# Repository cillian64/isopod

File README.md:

# ISOPOD

ISOPOD is a mobile interactive LED sculpture based on a 2.1m geodesic
isocahedron.  It was displayed at [EMF 2022](https://www.emfcamp.org/).

The outer shell is a 2V geodesic isocahedron made from custom-designed 3d
printed hubs and plastic water pipe.  The core is a regular icosahedron.  12
LED tubes connect to the core's vertices, each made from frosted acrylic tube
and containing a WS2812b addressable LED strip.

The core contains a battery, control electronics, and DC-DC converters.  ISOPOD
is controlled by a Raspberry Pi running software written in Rust.  A custom PCB
mounted on the Pi connects to the battery, DC-DC converters, and LED strips and
adds a battery fuel gauge, GPS module, and 9-axis IMU (accelerometer,
gyroscope, and magnetometer).

ISOPOD was displayed at EMF 2022 with a tether cable (to extend battery life
and avoid it rolling downhill into the lake) but is designed to be totally
wireless, reporting its position and status over Wi-Fi to a backend server.

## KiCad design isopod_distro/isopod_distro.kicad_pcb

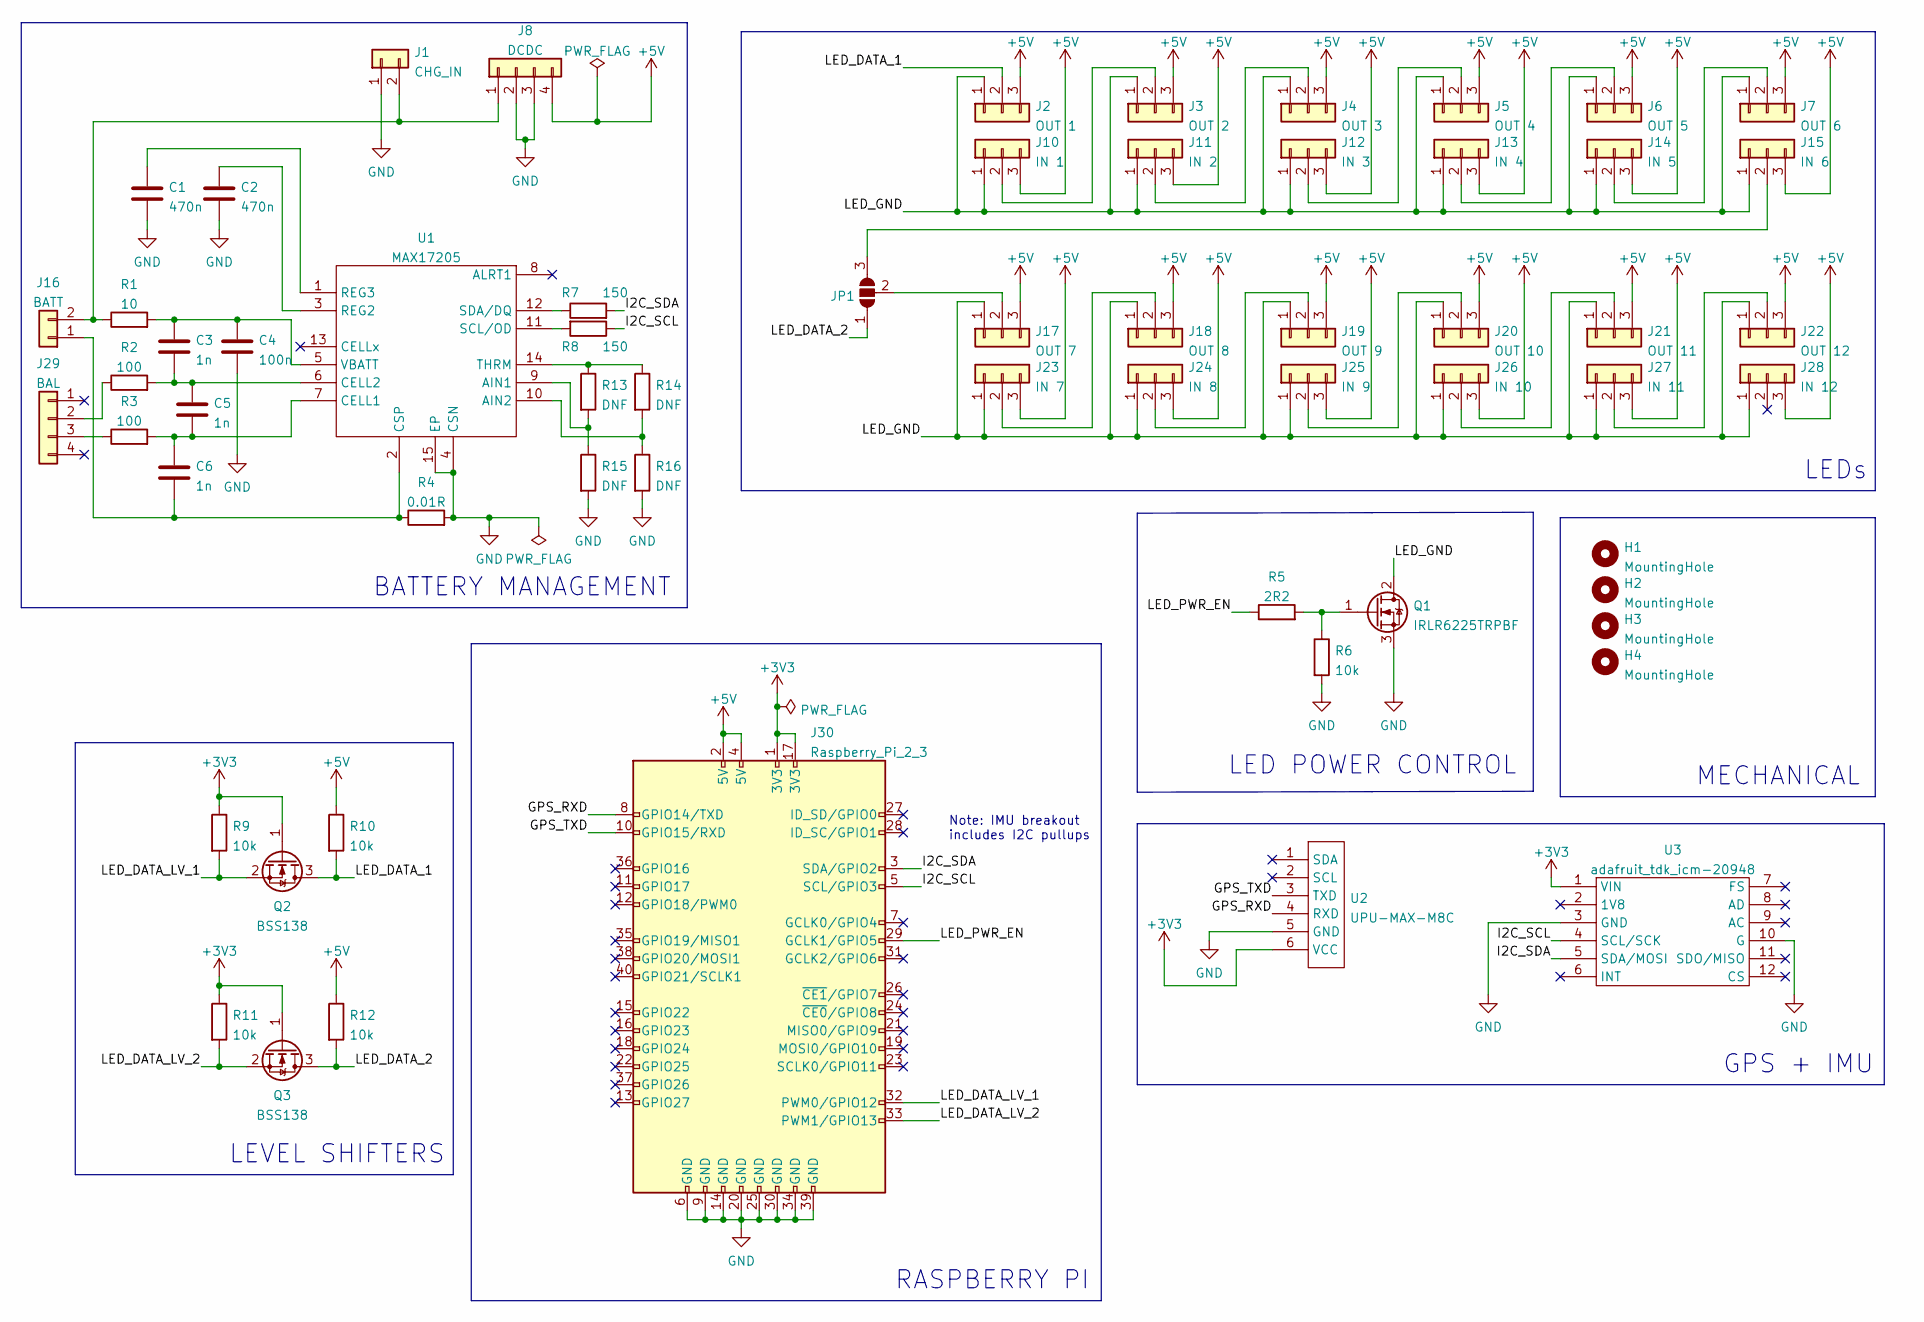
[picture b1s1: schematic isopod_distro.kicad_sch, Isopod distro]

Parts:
C1, C2: 470n; C_0603_1608Metric_Pad1.08x0.95mm_HandSolder
C3, C5, C6: 1n; C_0603_1608Metric_Pad1.08x0.95mm_HandSolder
C4: 100n; C_0603_1608Metric_Pad1.08x0.95mm_HandSolder
H1, H2, H3, H4: MountingHole; MountingHole_2.7mm
J1: CHG_IN; AMASS_XT30U-M_1x02_P5.0mm_Vertical
J2: OUT 1; Molex_KK-254_AE-6410-03A_1x03_P2.54mm_Vertical
J3: OUT 2; Molex_KK-254_AE-6410-03A_1x03_P2.54mm_Vertical
J4: OUT 3; Molex_KK-254_AE-6410-03A_1x03_P2.54mm_Vertical
J5: OUT 4; Molex_KK-254_AE-6410-03A_1x03_P2.54mm_Vertical
J6: OUT 5; Molex_KK-254_AE-6410-03A_1x03_P2.54mm_Vertical
J7: OUT 6; Molex_KK-254_AE-6410-03A_1x03_P2.54mm_Vertical
J8: DCDC; Molex_Mini-Fit_Jr_5566-04A_2x02_P4.20mm_Vertical
J10: IN 1; Molex_KK-254_AE-6410-03A_1x03_P2.54mm_Vertical
J11: IN 2; Molex_KK-254_AE-6410-03A_1x03_P2.54mm_Vertical
J12: IN 3; Molex_KK-254_AE-6410-03A_1x03_P2.54mm_Vertical
J13: IN 4; Molex_KK-254_AE-6410-03A_1x03_P2.54mm_Vertical
J14: IN 5; Molex_KK-254_AE-6410-03A_1x03_P2.54mm_Vertical
J15: IN 6; Molex_KK-254_AE-6410-03A_1x03_P2.54mm_Vertical
J16: BATT; AMASS_XT30U-M_1x02_P5.0mm_Vertical
J17: OUT 7; Molex_KK-254_AE-6410-03A_1x03_P2.54mm_Vertical
J18: OUT 8; Molex_KK-254_AE-6410-03A_1x03_P2.54mm_Vertical
J19: OUT 9; Molex_KK-254_AE-6410-03A_1x03_P2.54mm_Vertical
J20: OUT 10; Molex_KK-254_AE-6410-03A_1x03_P2.54mm_Vertical
J21: OUT 11; Molex_KK-254_AE-6410-03A_1x03_P2.54mm_Vertical
J22: OUT 12; Molex_KK-254_AE-6410-03A_1x03_P2.54mm_Vertical
J23: IN 7; Molex_KK-254_AE-6410-03A_1x03_P2.54mm_Vertical
J24: IN 8; Molex_KK-254_AE-6410-03A_1x03_P2.54mm_Vertical
J25: IN 9; Molex_KK-254_AE-6410-03A_1x03_P2.54mm_Vertical
J26: IN 10; Molex_KK-254_AE-6410-03A_1x03_P2.54mm_Vertical
J27: IN 11; Molex_KK-254_AE-6410-03A_1x03_P2.54mm_Vertical
J28: IN 12; Molex_KK-254_AE-6410-03A_1x03_P2.54mm_Vertical
J29: BAL; JST_XH_B4B-XH-AM_1x04_P2.50mm_Vertical
J30: Raspberry_Pi_2_3; PinHeader_2x20_P2.54mm_Vertical
JP1: SolderJumper_3_Open; SolderJumper-3_P1.3mm_Bridged12_RoundedPad1.0x1.5mm
Q1: IRLR6225TRPBF; TO-252-2; Farnell 2726021
Q2, Q3: BSS138; SOT-23
R1: 10; R_0805_2012Metric_Pad1.20x1.40mm_HandSolder
R2, R3: 100; R_0805_2012Metric_Pad1.20x1.40mm_HandSolder
R4: 0.01R; R_1206_3216Metric_Pad1.30x1.75mm_HandSolder
R5: 2R2; R_0603_1608Metric_Pad0.98x0.95mm_HandSolder
R6, R9, R10, R11, R12: 10k; R_0603_1608Metric_Pad0.98x0.95mm_HandSolder
R7, R8: 150; R_0603_1608Metric_Pad0.98x0.95mm_HandSolder
R13, R14, R15, R16: DNF; R_0603_1608Metric_Pad0.98x0.95mm_HandSolder
U1: MAX17205; TDFN-14-1EP_3x3mm_P0.4mm_EP1.78x2.35mm; Farnell 3404585
U2: UPU-MAX-M8C; upu-max-m8c
U3: adafruit_tdk_icm-20948; adafruit-tdk-icm-20948

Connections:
+3V3: J30.1 (3V3), J30.17 (3V3), Q2.1 (G), Q3.1 (G), R9.1, R11.1, U2.6 (VCC), U3.1 (VIN)
+5V: J2.3, J3.3, J4.3, J5.3, J6.3, J7.3, J8.4, J10.3, J11.3, J12.3, J13.3, J14.3, J15.3, J17.3, J18.3, J19.3, J20.3, J21.3, J22.3, J23.3, J24.3, J25.3, J26.3, J27.3, J28.3, J30.2 (5V), J30.4 (5V), R10.1, R12.1
/GPS_RXD: J30.8 (GPIO14/TXD), U2.4 (RXD)
/GPS_TXD: J30.10 (GPIO15/RXD), U2.3 (TXD)
/I2C_SCL: J30.5 (SCL/GPIO3), R8.1, U3.4 (SCL/SCK)
/I2C_SDA: J30.3 (SDA/GPIO2), R7.2, U3.5 (SDA/MOSI)
/LED_DATA_1: J2.2, Q2.3 (D), R10.2
/LED_DATA_2: JP1.1 (A), Q3.3 (D), R12.2
/LED_DATA_LV_1: J30.32 (PWM0/GPIO12), Q2.2 (S), R9.2
/LED_DATA_LV_2: J30.33 (PWM1/GPIO13), Q3.2 (S), R11.2
/LED_GND: J2.1, J3.1, J4.1, J5.1, J6.1, J7.1, J10.1, J11.1, J12.1, J13.1, J14.1, J15.1, J17.1, J18.1, J19.1, J20.1, J21.1, J22.1, J23.1, J24.1, J25.1, J26.1, J27.1, J28.1, Q1.2 (D)
/LED_PWR_EN: J30.29 (GCLK1/GPIO5), R5.1
GND: C1.2, C2.2, C4.2, J1.1, J8.2, J8.3, J30.6 (GND), J30.9 (GND), J30.14 (GND), J30.20 (GND), J30.25 (GND), J30.30 (GND), J30.34 (GND), J30.39 (GND), Q1.3 (S), R4.2, R6.2, R15.2, R16.2, U1.4 (CSN), U1.15 (EP), U2.5 (GND), U3.3 (GND), U3.10 (G)
unnamed: C1.1, U1.1 (REG3)
unnamed: C2.1, U1.3 (REG2)
unnamed: C3.1, C4.1, R1.2, U1.5 (VBATT)
unnamed: C3.2, C5.1, R2.2, U1.6 (CELL2)
unnamed: C5.2, C6.1, R3.2, U1.7 (CELL1)
unnamed: C6.2, J16.1, R4.1, U1.2 (CSP)
unnamed: J1.2, J8.1, J16.2, R1.1
unnamed: J3.2, J10.2
unnamed: J4.2, J11.2
unnamed: J5.2, J12.2
unnamed: J6.2, J13.2
unnamed: J7.2, J14.2
unnamed: J15.2, JP1.3 (B)
unnamed: J17.2, JP1.2 (C)
unnamed: J18.2, J23.2
unnamed: J19.2, J24.2
unnamed: J20.2, J25.2
unnamed: J21.2, J26.2
unnamed: J22.2, J27.2
unnamed: J29.2, R2.1
unnamed: J29.3, R3.1
unnamed: Q1.1 (G), R5.2, R6.1
unnamed: R7.1, U1.12 (SDA/DQ)
unnamed: R8.2, U1.11 (SCL/OD)
unnamed: R13.1, R14.1, U1.14 (THRM)
unnamed: R13.2, R15.1, U1.9 (AIN1)
unnamed: R14.2, R16.1, U1.10 (AIN2)

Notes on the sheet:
LED POWER CONTROL
BATTERY MANAGEMENT
LEVEL SHIFTERS
LEDs
MECHANICAL
GPS + IMU
RASPBERRY PI
Note: IMU breakout includes I2C pullups

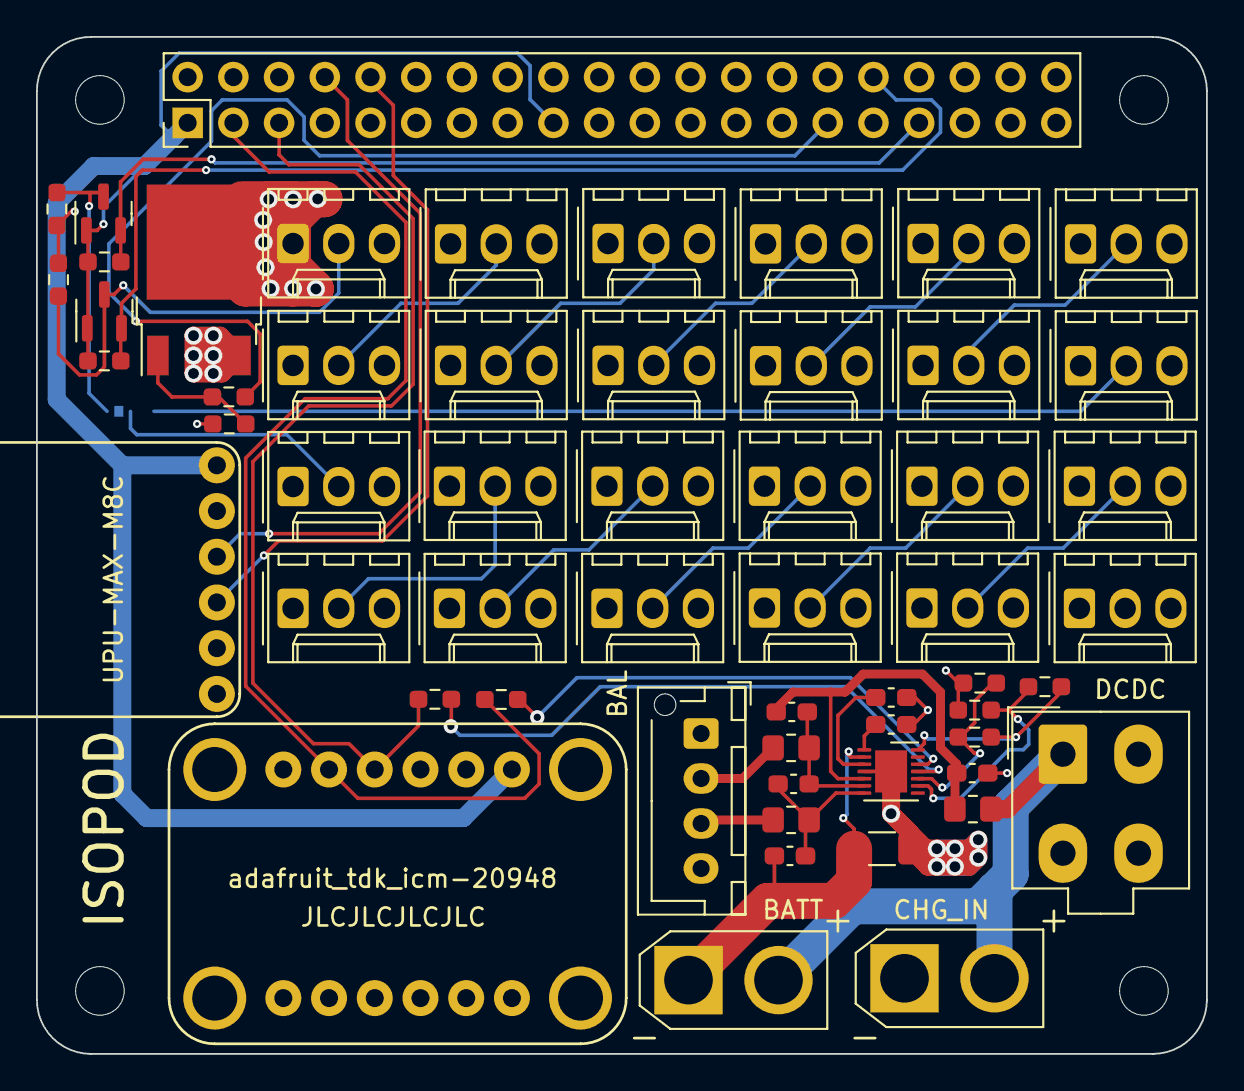
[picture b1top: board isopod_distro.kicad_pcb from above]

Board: 4 copper layers, 65.0 x 56.5 mm, 62 parts (1 on the bottom side), 40 nets.

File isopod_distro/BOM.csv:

Comment,Designator,Footprint,LCSC,Qty/board,Qty
BAL,J29,JST_XH_B4B-XH-AM_1x04_P2.50mm_Vertical,C594233,1,2
Raspberry_Pi_2_3,J30,PinHeader_2x20_P2.54mm_Vertical,C132132,1,2
100n,C4,C_0603_1608Metric_Pad1.08x0.95mm_HandSolder,C14663,1,5
0.01R,R4,R_1206_3216Metric_Pad1.30x1.75mm_HandSolder,C154635,1,5
1n,"C3,C5,C6",C_0603_1608Metric_Pad1.08x0.95mm_HandSolder,C1588,3,10
470n,"C1,C2",C_0603_1608Metric_Pad1.08x0.95mm_HandSolder,C1623,2,10
100,"R2,R3",R_0805_2012Metric_Pad1.20x1.40mm_HandSolder,C17408,2,10
10,R1,R_0805_2012Metric_Pad1.20x1.40mm_HandSolder,C17734,1,5
150,"R7,R8",R_0603_1608Metric_Pad0.98x0.95mm_HandSolder,C22808,2,10
2R2,R5,R_0603_1608Metric_Pad0.98x0.95mm_HandSolder,C22939,1,5
10k,"R10,R11,R12,R6,R9",R_0603_1608Metric_Pad0.98x0.95mm_HandSolder,C23192,5,15
MAX17205,U1,TDFN-14-1EP_3x3mm_P0.4mm_EP1.78x2.35mm,C401140,1,3
BSS138,"Q2,Q3",SOT-23,C75547 ,2,10
DCDC,J8,Molex_Mini-Fit_Jr_5566-04A_2x02_P4.20mm_Vertical,C47233,1,5
IN 1,"J10,J11,J12,J13,J14,J15,J17,J18,J19,J2,J20,J21,J22,J23,J24,J25,J26,J27,J28,J3,J4,J5,J6,J7",Molex_KK-254_AE-6410-03A_1x03_P2.54mm_Vertical,C706936,24,24
CHG_IN,"J1,J16",AMASS_XT30U-M_1x02_P5.0mm_Vertical,C99101,2,2

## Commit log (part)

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2022-02-13 Rough draft of distro board schematic
2022-02-19 First draft of schematic and pcb placement
    Finish first draft of schematic:
    * Replace relay with hexFET switch
    * Replace battery monitoring tap with fuel gauge / balance IC
    * Fill in various values
    * Pi pin assigments
    * Footprint assignments
2022-02-20 Assign footprints for fuel gauge resistors
2022-02-20 Start routing PCB
2022-02-25 SW: Basic rust peripheral demo
    * Add the beginnings of the rust software
    * Basic peripheral test program which tests the IMU and GPS modules (and
    therefore the UART and I2C interfaces).
2022-03-05 3-pin connectors for LED return, reroute
    * Use 3-pin connectors for LED return so we can supply power at both
    ends of the LED strip
    * Juggle placement of the PCB again
    * First draft of PCB routing
2022-03-06 Swap out batt/charge and DC-DC connectors
    Use XT30 for battery and charge connectors and MOLEX mini-fit jr 4-way
    for the DC-DC converter connection
2022-03-19 Final schematic checks
    * Add some DNF resistors for the fuel cell in case its temperature
    sensing can't be disabled
    * Add some series resistors on I2C because the appnote says so
2022-03-19 Update PCB with schematic changes
    Add the new DNF resistors
2022-03-21 DRC fixes, further refinement
2022-03-24 Update PCB STEP model
2022-03-24 DRC fixes/exclusions
2022-03-24 Add JLC order marking, BOM, gerbs
    * Add JLCJLCJLCJLC location for order number
    * Add JLC/LCSC BOM database
    * Add finished gerbers
2022-03-25 Final BOM
2022-04-07 First draft of skeleton of firmware architecture
2022-04-09 Rainbow LEDs at the same time as UART+I2C
    Check for DMA collisions by smoothly fading LEDs at the same time as
    reading the GPS data over UART and regularly polling the I2C IMU sensor.
2022-04-09 Proof-of-concept location reporter
    * Store the GPS fix each time we get a fix
    * Periodically send the fix to the reporter thread
    * Reporter thread JSONifies the fix and sends it over HTTPS to the
    backend
2022-04-09 Update reporter URL
2022-04-09 Basic proof-of-concept reporter server
    * Receives reports
    * Deserializes the JSON into a nice Fix struct
    * Prints it out.
2022-04-09 Reporter should use POST, not PUT.
2022-04-13 Basic map location/path overlay in JS
    Basic javascript to plot the isopod location and path on top of the base
    map
2022-04-14 Basic geometry for javascript simulator
2022-04-15 Basic proof-of-concept websockets sending LED data
2022-04-15 Move camera positions closer in
2022-04-15 Prototype: Send LED states from main thread
    Generate LED pattern in main thread and send it to the LED and WS
    threads. This doesn't actually work currently, is a WIP.
2022-04-16 Ignore WS channel errors, add build script
    * Ignore mysterious errors from the tokio broadcast channel used for WS
    LED updates
    * Disable startup tests for now
    * Add script to cross-compile software, SCP it over to beacon, and run
    it.
2022-04-16 First draft of pattern trait interface
    * Add the Pattern trait to be used for patterns
    * Add a Zoom pattern as an example of using this
    * Do a little bit of other renaming/cleanup:
    * Rename Fix to GpsFix
    * Add an ImuReadings struct for IMU readings
2022-04-16 Add units to GPS fix and accelerometer data
2022-04-16 Actually record/provide IMU readings
2022-04-17 "shock" pattern: demo pattern depending on IMU
    Basic demonstrator pattern which illuminates all the LEDs if
    acceleration exceeds a certain threshold. Uses a moving average to
    ignore gravity or other constant offset.
2022-04-17 LED FPS improvement
    * Modify the LED channel reader to discard all but the latest message in
    the channel.
    * This means that if the LED renderer thread falls behind the pattern
    generator then we drop updates instead of falling behind and growing
    the channel buffer indefinitely.
    * This also means we get a warning message if we fall behind.
2022-04-21 Name the threads
    Helps with profiling in htop and also debugging backtraces. Pity you
    can't seem to name the main thread.
2022-04-21 Move JSONifying to a new thread
    Previously JSONifying the LED data was done separately for each
    websocket handler. This took up 30% of a CPU core per websocket so is a
    lot of load if multiple websockets are connected. But we don't want to
    do this in led_update which would burden the main thread with this. So
    make a new JSONifier thread which receives LedUpdates from the main
    thread, turns them into JSON, then broadcasts them to all the websocket
2022-04-21 Add config file
    Read a simple config file to determine some things so I don't have to
    keep recompiling to twiddle settings. Current settings:
    * FPS
    * Enable/disable websocket server
    * Enable/disable start-up tests
2022-04-22 Select static pattern from config file
    Add a new config file entry to select a single static pattern. Allows
    changing pattern without recompilation, useful for testing
2022-04-22 Use a hashmap of function ptrs to store patterns
    This way means that we don't unnecessarily initialise all patterns at
    startup, and can more easily reinitialise a pattern when switching back
    to it for the second time.
2022-04-22 Format google maps link for backend fix reports
2022-04-22 Add strip test pattern
2022-04-26 Log battery status and report to backend
    Integrate the new MAX1720x crate to read the battery status from the
    fuel gauge IC, log the battery status, and report it to the backend
    server
2022-04-29 Add geometry lib and the searchlight pattern
    The pattern isn't very good but it's a reasonable demo of how to use the
    geometry library to do this sort of thing.
2022-04-29 Add "glitch" pattern
2022-04-29 Add handling for LED_ENABLE pin
    * Add new pattern which flashes an LED barely on and off to test the LED
    enabling/disabling code
    * Add LEDs enabling/disabling code. This has a bit of extra complexity
    because we need to force the PWM0 and PWM1 signals to go to VCC
    otherwise the LED strips will parasiticly power themselves by
    grounding through these data connections
2022-05-07 Load LED strip brightness from config file
2022-05-07 Update spines to only have 59 LEDs, not 60
2022-05-08 Fixup previous commit for no-hardware sim mode
    Also cargo fmt
2022-05-08 Add starfield pattern
2022-05-08 Add colourfield pattern
2022-05-08 Add battery details to backend packet parser
2022-05-08 Add core temperature logging to reporter
2022-05-08 Add new colourwipes pattern
2022-05-11 Rough out the PatternManager
    This is a new struct which will control pattern selection and
    transitions. It provides an interface pretty similar to Pattern
2022-05-12 Implement Default for LedUpdate
2022-05-15 Add some useful helper methods to ImuReadings
2022-05-15 Attempt 1: integer beans
    attempt 1 kinda almost works but has a bad time when beans are moving in
    the opposite direction to their acceleration (e.g. due to inertia)
2022-05-15 Attempt 2
    - Use floating positions and next_position
    - Do two collision passes in opposing directions depending on particle
    direction of movement
    - Apply all physics steps simultaneously
2022-05-15 Attempt 3: it works!!
    Basically re-doing the first attempt but:
    - Using floating point positions (from attempt 2)
    - Doing multiple small time steps per frame to mask some oddness in the
    way the physics simulation works
    - Add a little randomness to each velocity to break up solid clumps of
    beans so they don't just slide together
2022-05-16 Bugfix in pattern manager static patterns
    The settings reader can only return owned strings, not string
    references, and attempting the latter gives a runtime error which I
    mistook for the option not being specified.
2022-05-16 Implement Beans pattern
2022-05-16 Implement bean simulator
    Implement a basic command-line bean simulator to test out my bean
    physics.
2022-05-16 Implement Beans pattern
    Turn the command-line bean simulator into a physics library which is
    used by the actual beans pattern (and move the command-line part to a
    new binary for testing purposes).
2022-05-16 Select stationary patterns according to orientation
    Do a really simple method by splitting up the possible orientations into
    8 zones based on the sign of each accelerometer axis.
2022-05-16 Cargo fmt and clippify
2022-05-21 Fix a camera control bug in visualiser
2022-05-21 Viz: make ground more obvious, add axis markers
2022-05-21 Add LED mapping
    Add a map from connector numbers on the PCB to spine positions on the
    icosahedron, stored in the config file. This means it doesn't matter
    which hole the LED cables go to so long as we write down the mapping.
2022-05-21 Add viz->accel space rotation
    * Add a function to rotate vectors from the visualiser coordinate system
    to the accelerometer coordinate system
    * Apply this rotation to each spine direction vector so that these are
    now in accelerometer-aligned coordinates.
    * Reduce beans physics steps/frame to suit raspberry pi
2022-05-22 Add scripts to build on chonker
    This is a remote build server for use at EMF
2022-05-22 Chonker cross-compiler: abort on errors
2022-05-23 Second attempt at pattern manager
    * Split out motion sensing and circular buffer into new modules
    * Fast and slow LPF filter buffers for detecting fast and slow motion
    * Configurable thresholds for everything
    * Time since last motion counter for timing out the motion pattern
2022-05-24 Add sleep-mode pattern and patternmanager handling
2022-05-27 Fix bug in vector norm function
    That is definitely not how you calculate the 2-norm of a vector...
2022-05-27 Reset creep buffer after any fast movements
2022-05-27 Tune motion-sensor values
2022-05-27 Add state-change prints to pattern manager
2022-05-28 Timeout movement pattern based on bean stacking
    It's annoying if the movement pattern times out when you're trying to
    perfectly balance your beans. So, instead, time out the movement
    pattern if the beans all sit stacked at one end or the other for too
    long. Downside means if you don't tilt things enough to move the beans,
    it will just timeout. Upside means it will never time out when you're
    balancing it carefully. All resting positions on the outer icosphere
2022-05-28 Transition-out by sliding towards centre
    Seems a bit cooler than the current fade-out
2022-05-28 Start beans at centre instead of 0-end
    Seems a bit neater to start in an axisymmetric state, also this is the
    first step towards having the beans slide-out from the centre
2022-05-28 Slide out beans from centre at start of beans pattern
2022-05-29 Add wormholes pattern
2022-05-31 Change bean colours after 2s unstacked
    If the beans in a tube spend 2s (120 frames) not stacked at either end
    then randomly change all their colours to a new random colour
2022-05-31 Add sparkles pattern
2022-06-02 Add systemd service
2022-06-04 Jukebox: shuffle and transition
    Change jukebox mode to use a real transition between patterns and to
    randomly shuffle which pattern comes up next
2022-06-04 Increase jukebox timer to 1 minute
2022-12-19 Update README and add photos
2023-04-08 Add rainbow swirl pattern
2023-04-08 cargo fmt
2023-04-08 Try really hard to disable LTO
2023-04-08 Remove redundant theta smear parameter from rainbow swirl
2023-07-23 Disable LTO for faster compile time
2023-07-23 Add frame-skip to starfield
2023-09-09 Update static patterns comments
2023-09-09 Clean up compile warnings
2023-09-09 Add skeleton of control web server
    Super basic web server providing web frontend to configure a few aspects
    at runtime.
2023-09-09 Control LED brightness via web UI
